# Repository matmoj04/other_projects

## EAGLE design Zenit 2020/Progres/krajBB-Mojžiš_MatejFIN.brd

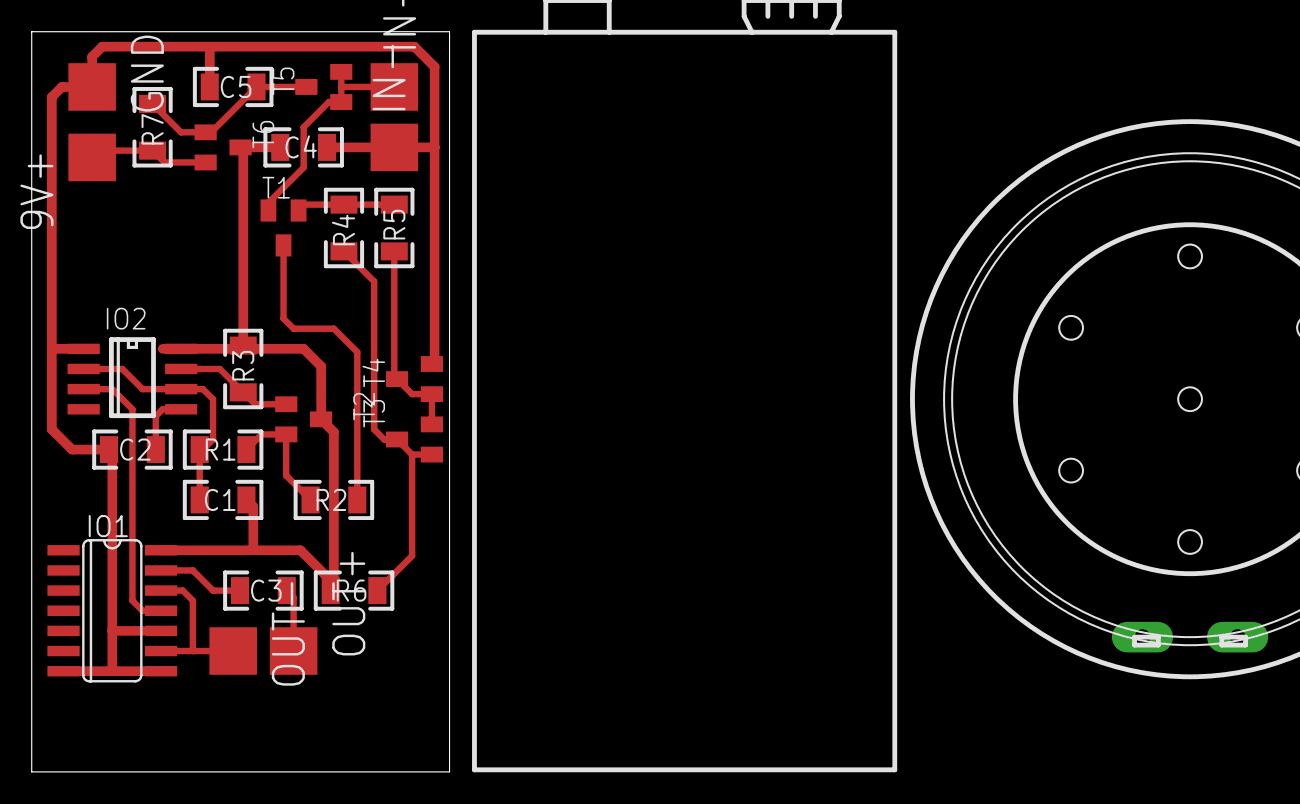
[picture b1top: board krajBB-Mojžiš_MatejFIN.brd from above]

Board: 2 copper layers, 26.3 x 46.7 mm, 28 parts (0 on the bottom side), 17 nets.

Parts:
9V+: SMD3X3
C1, C2, C3, C4, C5: 1u; 1206
GND: SMD3X3
IN+: SMD3X3
IN-: SMD3X3
IO1: 4013D; SO14
IO2: NE555D; SO08
OUT+: SMD3X3
OUT-: SMD3X3
R1: 100; 1206
R2: 470; 1206
R3, R4: 10k; 1206
R5: 2.2k; 1206
R6: 47k; 1206
R7: 10M; 1206
REPRODUKTOR: LD-DR-3519
T1, T2, T3, T4: BC817-25; SOT23-BEC
T5, T6: BSS84; SOT23
U$1: 9VBATTERY

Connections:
9V_1: R4.2, R6.1, T3.B, T3.C
9V_2: R5.1, T3.E, T4.B, T4.C
+9V: C1.2, C4.2, IO1.14, IO2.4, IO2.8, R3.2, R6.2, T2.C, T6.3
CLOCK: IO1.11, IO2.3
CV: C2.2, IO2.5
DIS: IO2.7, R3.1, T2.B
DIS_1: R2.1, T1.C
DIS_IN: R1.1, R2.2, T2.E
DIV: R4.1, R5.2, T1.B
GND: C2.1, C4.1, C5.1, GND.P$1, IN-.P$1, IO1.7, IO1.8, IO1.10, IO2.1, T4.E
IN: IN+.P$1, T1.E, T5.1, T5.2
MOS: C5.2, R7.1, T5.3, T6.1
OUT: C3.1, IO1.13
REP: C3.2, OUT+.P$1
REP+: IO1.9, IO1.12, OUT-.P$1
THR: C1.1, IO2.2, IO2.6, R1.2
VIN: 9V+.P$1, R7.2, T6.2
